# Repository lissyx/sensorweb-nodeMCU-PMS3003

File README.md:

NodeMCU PMS3003 PM2.5 Sensor
============================

This repo aims at providing a PM2.5 (and others) sensor that pushes data to the
Internets, namely AirCasting API. It uses a PMS3003 + NodeMCU v1.0 (ESP-12E), as
it was built as a side-project to augment (now defunct) Mozilla SensorWeb
project with something that could be autonomous and outdoor.

Good Known Setup
================
 - Arduino IDE 1.8.8
 - ESP8266 Package v2.4.2
 - ArduinoJson v5.13.5
 - NtpClientLib v2.5.1
 - Time v1.5
 - WiFiManager v0.14
 - ESP8266TrueRandom (any version?)
 - ESP8266FS.jar v0.3.0 (not a lib, need to be installed separately into tools/
   arduino subdir)

Ensure to configure board in Arduino IDE as:
 - NodeMCU 1.0 (ESP-12E)
 - 80MHz
 - Flash
 - 4M (3M SPIFFS)
 - v2 Lower Memory

Configuration
=============
For first flash, ensure you properly populate `data/` subdirectory with:
 - `wifi.json`
 - `ntp.json`
 - `aircasting.json`
Please follow the templates named <FILE>.in, copy them as the proper name under
`data/`. Then in Arduino IDE, flash using `Tools`, `ESP8266 Sketch Data Upload`.

Default configuration should be for AirCasting.org website, but it is expected
to work on any instance following their API.

Then you can build and flash. It should boot and work.

Debugging
=========
Serial debugging should work over USB. The same data is sent over the wire,
defaulting to UDP multicast address `239.0.0.1`, port `8899`.

Outdooring
==========
To be able to handle outdoor, original SensorWeb project has been augmented with
a power source. This leads to the design of a small PCB that serves several
purposes:
 - properly fitting / holding the NodeMCU with inline connectors
 - some logic to handle PMS3003 standby mode
 - proper connector for the PMS3003 wired to the NodeMCU pins
 - proper 5v: PMS3003 tends to be picky, working with less than 4v but giving
   inconsistent results

The power part of the PCB is inspired from Adafruit's Minty Boost:
https://learn.adafruit.com/minty-boost/overview

Solar power cannot be available 100% of the time, so it is battery-backed, using
the kit provided by Adafruit:
https://learn.adafruit.com/usb-dc-and-solar-lipoly-charger?view=all

Solar panel are also provided, though they can be found at a lot of different
places.

Any LiPo or LiIon should work.

Checkout the Kicad project for exact references.

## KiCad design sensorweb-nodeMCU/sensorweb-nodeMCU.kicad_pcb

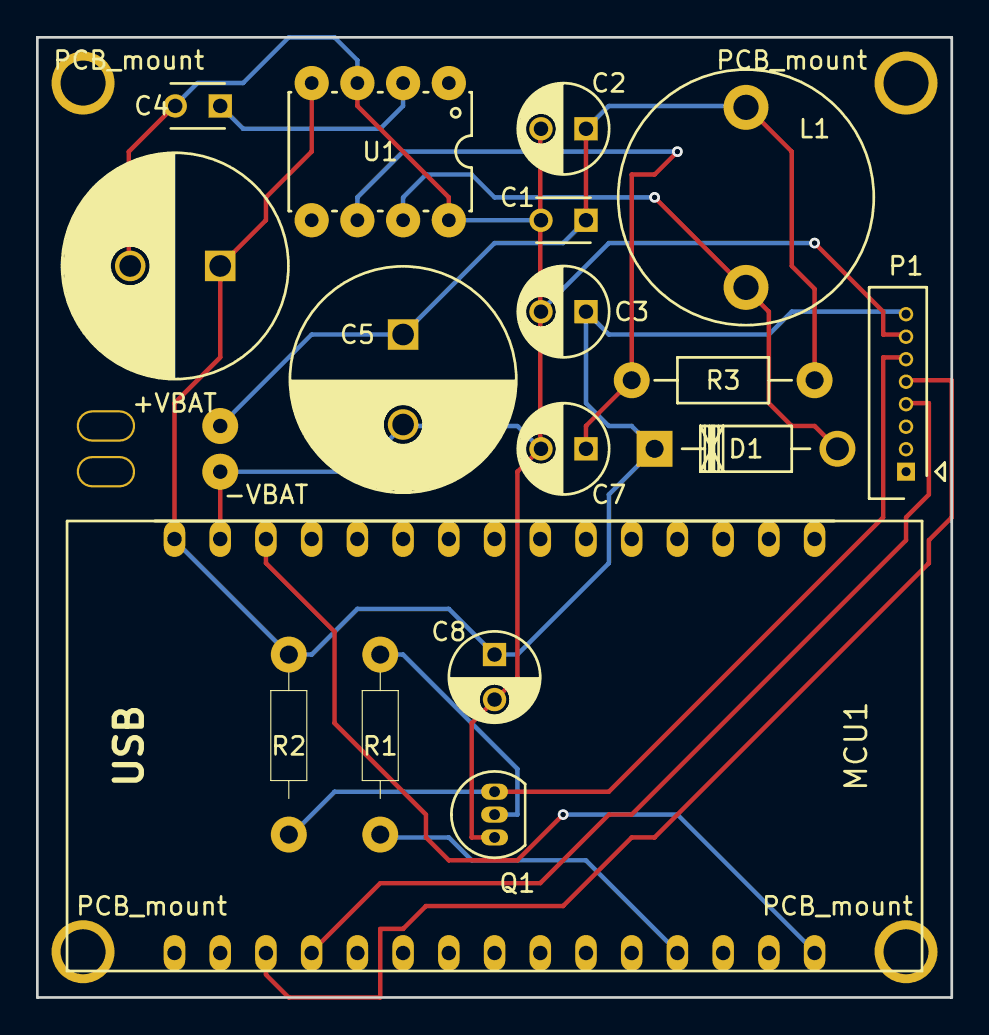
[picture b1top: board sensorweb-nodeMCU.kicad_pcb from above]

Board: 2 copper layers, 50.8 x 53.3 mm, 19 parts (0 on the bottom side), 12 nets.

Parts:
+VBAT: +VBAT; SolderWirePad_single_0-8mmDrill
-VBAT: -VBAT; SolderWirePad_single_0-8mmDrill
C1, C4: 0.1µF; C_Disc_D3_P2.5
C2, C3, C8: 220µF; C_Radial_D5_L6_P2.5
C5, C6: 4700µF; C_Radial_D12.5_L25_P5
C7: 1µF; C_Radial_D5_L6_P2.5
D1: 1N5817; Diode_DO-41_SOD81_Horizontal_RM10
L1: 22µH; Neosid_Inductor_Sd14
MCU1: NodeMCU-1.0; nodemcu
P1: PMS3003; Molex_PicoBlade_53047-0810
Q1: 2N2222; TO-92_Inline_Narrow_Oval
R1, R2: 10k; Resistor_Horizontal_RM10mm
R3: 2ohm / 10ohm; Resistor_Horizontal_RM10mm
U1: LT1302CN8-5; PDIP-8

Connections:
+5V: C3.1, C6.1, C8.1, D1.1, MCU1.15, P1.8, R2.1, U1.4
GND: -VBAT.1, C1.2, C2.2, C3.2, C4.2, C5.2, C6.2, C7.2, C8.2, MCU1.14, P1.7, Q1.1, U1.3, U1.8
unnamed: +VBAT.1, C1.1, C2.1, C5.1, L1.2, R3.1
unnamed: C4.1, U1.2
unnamed: C7.1, R3.2, U1.6
unnamed: D1.2, L1.1, U1.7
unnamed: MCU1.13, MCU1.30
unnamed: MCU1.18, P1.5
unnamed: MCU1.19, P1.4
unnamed: MCU1.27, R1.2
unnamed: P1.6, Q1.3, R2.2
unnamed: Q1.2, R1.1

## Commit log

2017-01-19 First commit with something somehow working.
2017-01-22 Add RTC slow down factor heuristic
2017-01-26 Apply proper timezone offset to produce UTC ISO8601
2017-01-27 Send 'Connection: Close' header
2017-01-27 Improve HTTP error reporting
2017-01-27 Trigger NTP only when needed
2017-02-14 Switching to AirCasting.org
2017-02-14 Send device hostname with UDP debug message
2017-02-14 AirCasting data push
2017-02-14 Move description to utility functions
2017-02-14 Support AirCasting HTTP/400 error and create new session
2017-02-14 Distinguish session per sensor
2017-02-14 Fix slowDownFactor
2017-02-14 Add NtpConfig singleton
2017-02-15 Send proper timezone and contribute flags to AirCasting
2017-02-16 Support ISO8601 UTC and non-UTC
2017-03-19 Send UDPv4 multicast packets
2017-03-19 Update schematics
2017-04-29 Add version and build timestamp to logs
2017-05-16 Fixing schematic and PCB
2017-05-18 Call WiFiMulti::run() on first cycle boot
2017-06-03 Serial ebug message on boot while waiting WiFi
2018-01-04 Force WiFi to 802.11n to reduce power pressure.
2018-09-26 LICENSE
2019-01-28 README.md documenting versions
2019-01-29 Fix crash with NtpClientLib v2.5.x and get lwIP variant v2
2019-01-29 Document NTP Sync stale event
2019-01-29 Be silent on no UDP Debug
2019-01-29 Ignore stale event with example
2019-02-21 Fix bogus field triggering HTTP/500 with new Rails version
2019-02-21 Fix error 500 when sending measurements after rails upgrade
2019-02-23 Set version 1.2
